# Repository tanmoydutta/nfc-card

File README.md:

# NFC Card — Temperature and Humidity Sensor

This project is built around **OSHWA-certified open source hardware**, certified under [NL000047](https://certification.oshwa.org/nl000047.html).

A phone-powered NFC sensor board for reading temperature and relative humidity. The board uses an NXP NTAG device and a Sensirion SHT40 sensor to take a measurement and return it to a mobile phone over NFC.

The intended sensing flow uses energy harvested from the phone's NFC field, allowing a reading without a battery or an external power supply.

## How it works

1. Bring an NFC-enabled mobile phone close to the board's antenna and start a read from the mobile app.
2. The phone's NFC field supplies energy to the board.
3. The phone triggers the NTAG to request a temperature and humidity measurement from the SHT40 over I²C.
4. The measurement is returned to the phone through the NFC interface.
5. The app displays temperature and relative humidity readings.

Keep the phone close to the antenna until the reading completes so the board continues to receive power and communicate.

## Hardware

- **NFC interface:** NXP NTP53321G0JHKZ NTAG device.
- **Sensor:** Sensirion SHT40 for digital temperature and relative humidity measurements.
- **Sensor connection:** I²C (SDA and SCL).
- **Power for phone-triggered readings:** Energy harvested from the mobile phone's NFC field.

## Repository contents

| Folder | Contents |
| --- | --- |
| `Design_Files/` | EAGLE schematic (`nfc-card.sch`) and PCB layout (`nfc-card.brd`). |
| `3D/` | Reserved for mechanical models and enclosure files. |
| `App/` | Reserved for mobile app source and related files. |
| `images/` | Schematic, board renders, board photo, app screenshot, and OSHW image. |

Open the schematic and board files together in an EAGLE-compatible PCB design tool to inspect or modify the hardware. The `App/` and `3D/` folders currently contain placeholders.

## Reading the sensor

Use an NFC-enabled phone with a compatible app that supports this board's measurement flow. Enable NFC where required, start a sensor read, and hold the phone's NFC antenna near the board's antenna. The app should present temperature and relative humidity after the measurement is received.

The app screenshot below illustrates the sensor-reading interface; app source and setup instructions are not yet included in this repository.

## Images

### Schematic

### Board renders

### Assembled board

### Mobile app sensor reading

### Open Source Hardware

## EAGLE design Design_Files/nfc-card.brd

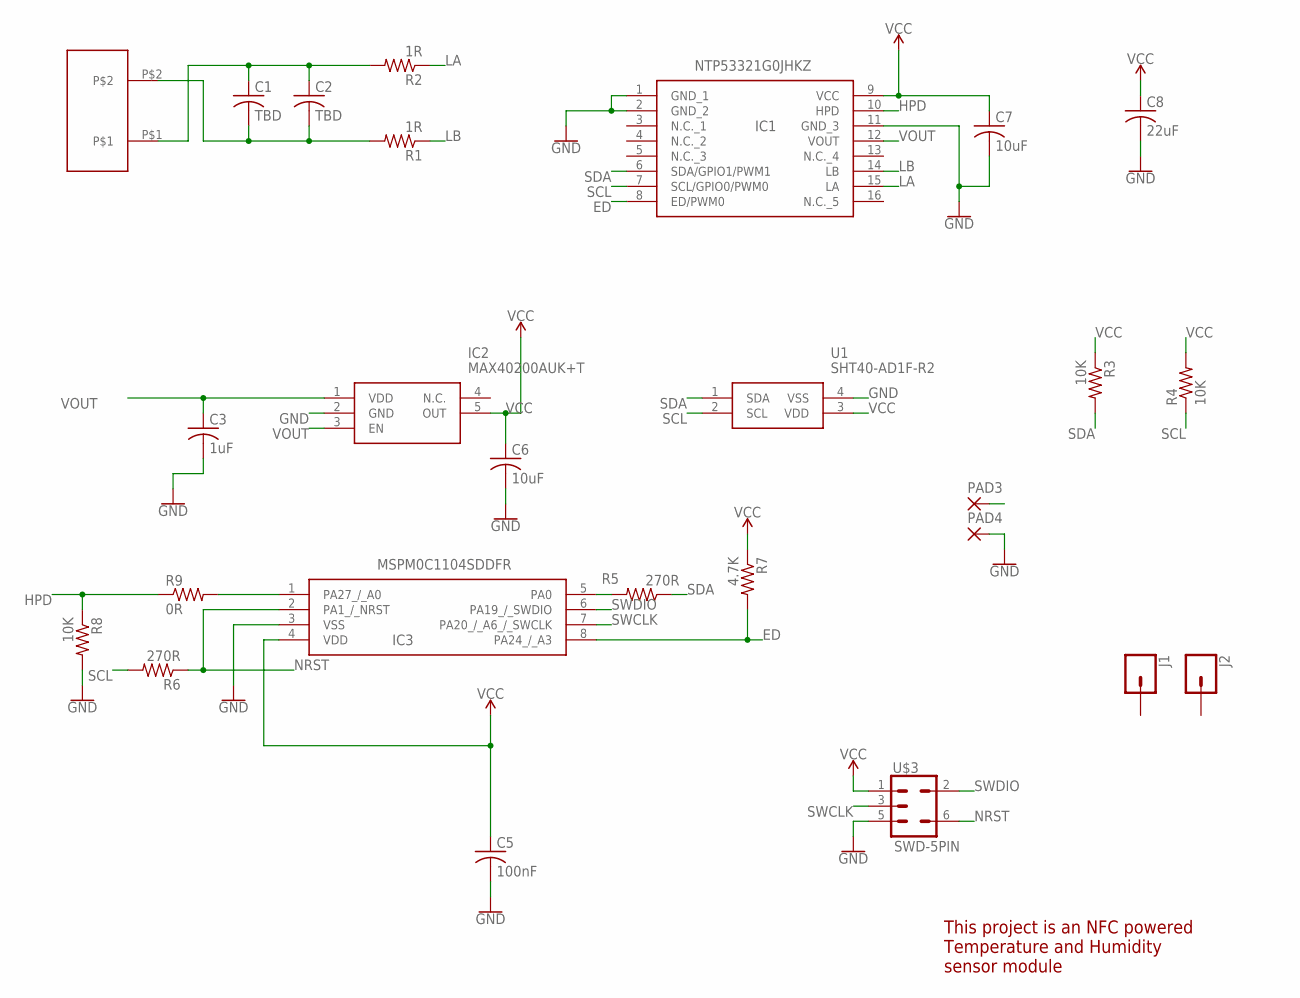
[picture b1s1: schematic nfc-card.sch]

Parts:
C1, C2: TBD; C0402
C3: 1uF; C0805
C5: 100nF; C0402
C6: 10uF; C0402
C7: 10uF; C0805
C8: 22uF; C1206
IC1: NTP53321G0JHKZ
IC2: MAX40200AUK+T; SOT95P280X145-5N
IC3: MSPM0C1104SDDFR; SOT65P280X110-8N
J1, J2: CONN_01PTH_2MM; 1X01_2MM
PAD3, PAD4: 1,6/0,8
R1, R2: 1R; R0402
R3, R4, R8: 10K; R0402
R5, R6: 270R; R0402
R7: 4.7K; R0402
R9: 0R; R0402
U1: SHT40-AD1F-R2; SHT40AD1FR2
U$2: NFC-POWER
U$3: SWD-5PIN; PAD_05_03X2_TP_NO4

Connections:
ED: IC1.8 (ED/PWM0), IC3.8 (PA24_/_A3), R7.2
GND: C3.2, C5.2, C6.2, C7.2, C8.2, IC1.1 (GND_1), IC1.2 (GND_2), IC1.11 (GND_3), IC2.2 (GND), IC3.3 (VSS), PAD4.1, R8.2, U1.4 (VSS), U$3.5
HPD: IC1.10 (HPD), R8.1, R9.1
LA: IC1.15 (LA), R2.1
LB: IC1.14 (LB), R1.1
unnamed: IC3.5 (PA0), R5.2
unnamed: IC3.1 (PA27_/_A0), R9.2
unnamed: C1.2, C2.2, R1.2, U$2.P$2
unnamed: C1.1, C2.1, R2.2, U$2.P$1
NRST: IC3.2 (PA1_/_NRST), R6.1, U$3.6
SCL: IC1.7 (SCL/GPIO0/PWM0), R4.1, R6.2, U1.2 (SCL)
SDA: IC1.6 (SDA/GPIO1/PWM1), R3.2, R5.1, U1.1 (SDA)
SWCLK: IC3.7 (PA20_/_A6_/_SWCLK), U$3.3
SWDIO: IC3.6 (PA19_/_SWDIO), U$3.2
VCC: C5.1, C6.1, C7.1, C8.1, IC1.9 (VCC), IC2.5 (OUT), IC3.4 (VDD), R3.1, R4.2, R7.1, U1.3 (VDD), U$3.1
VOUT: C3.1, IC1.12 (VOUT), IC2.1 (VDD), IC2.3 (EN), PAD3.1

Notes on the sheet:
This project is an NFC powered Temperature and Humidity sensor module

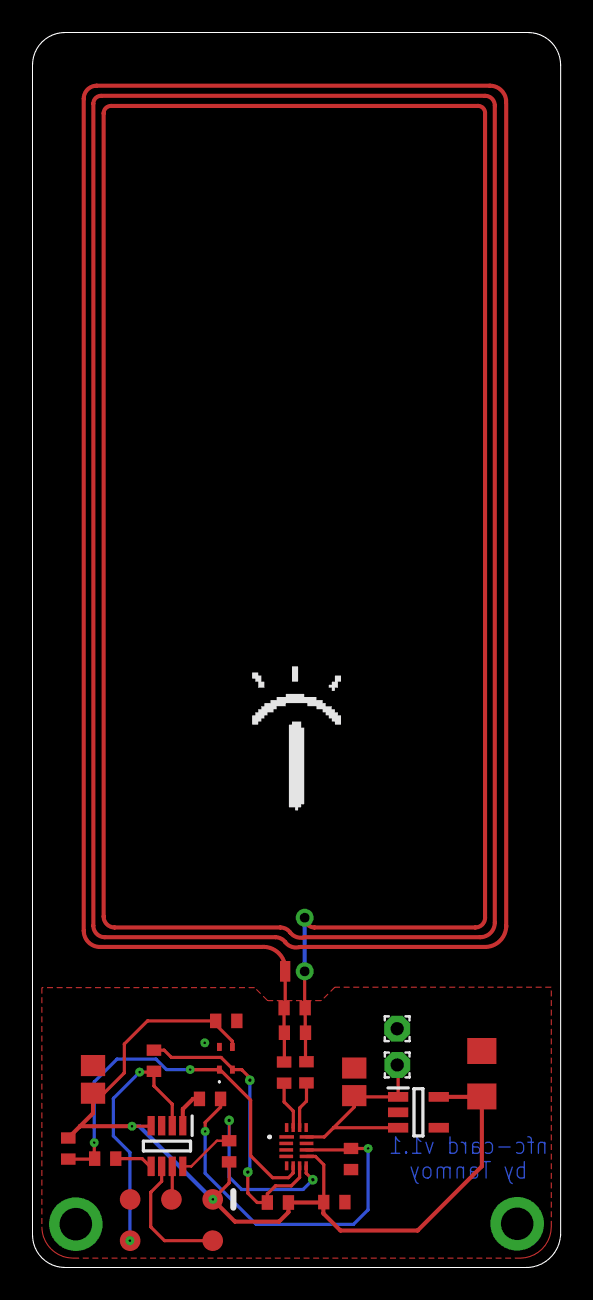
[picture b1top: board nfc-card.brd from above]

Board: 2 copper layers, 32.5 x 76.0 mm, 26 parts (0 on the bottom side), 16 nets.

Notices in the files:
README.md:
Open Source Hardware license
parts and their libraries:
SparkFun-Connectors: Licensing: Creative Commons ShareAlike 4.0 International - https://creativecommons.org/licenses/by-sa/4.0
